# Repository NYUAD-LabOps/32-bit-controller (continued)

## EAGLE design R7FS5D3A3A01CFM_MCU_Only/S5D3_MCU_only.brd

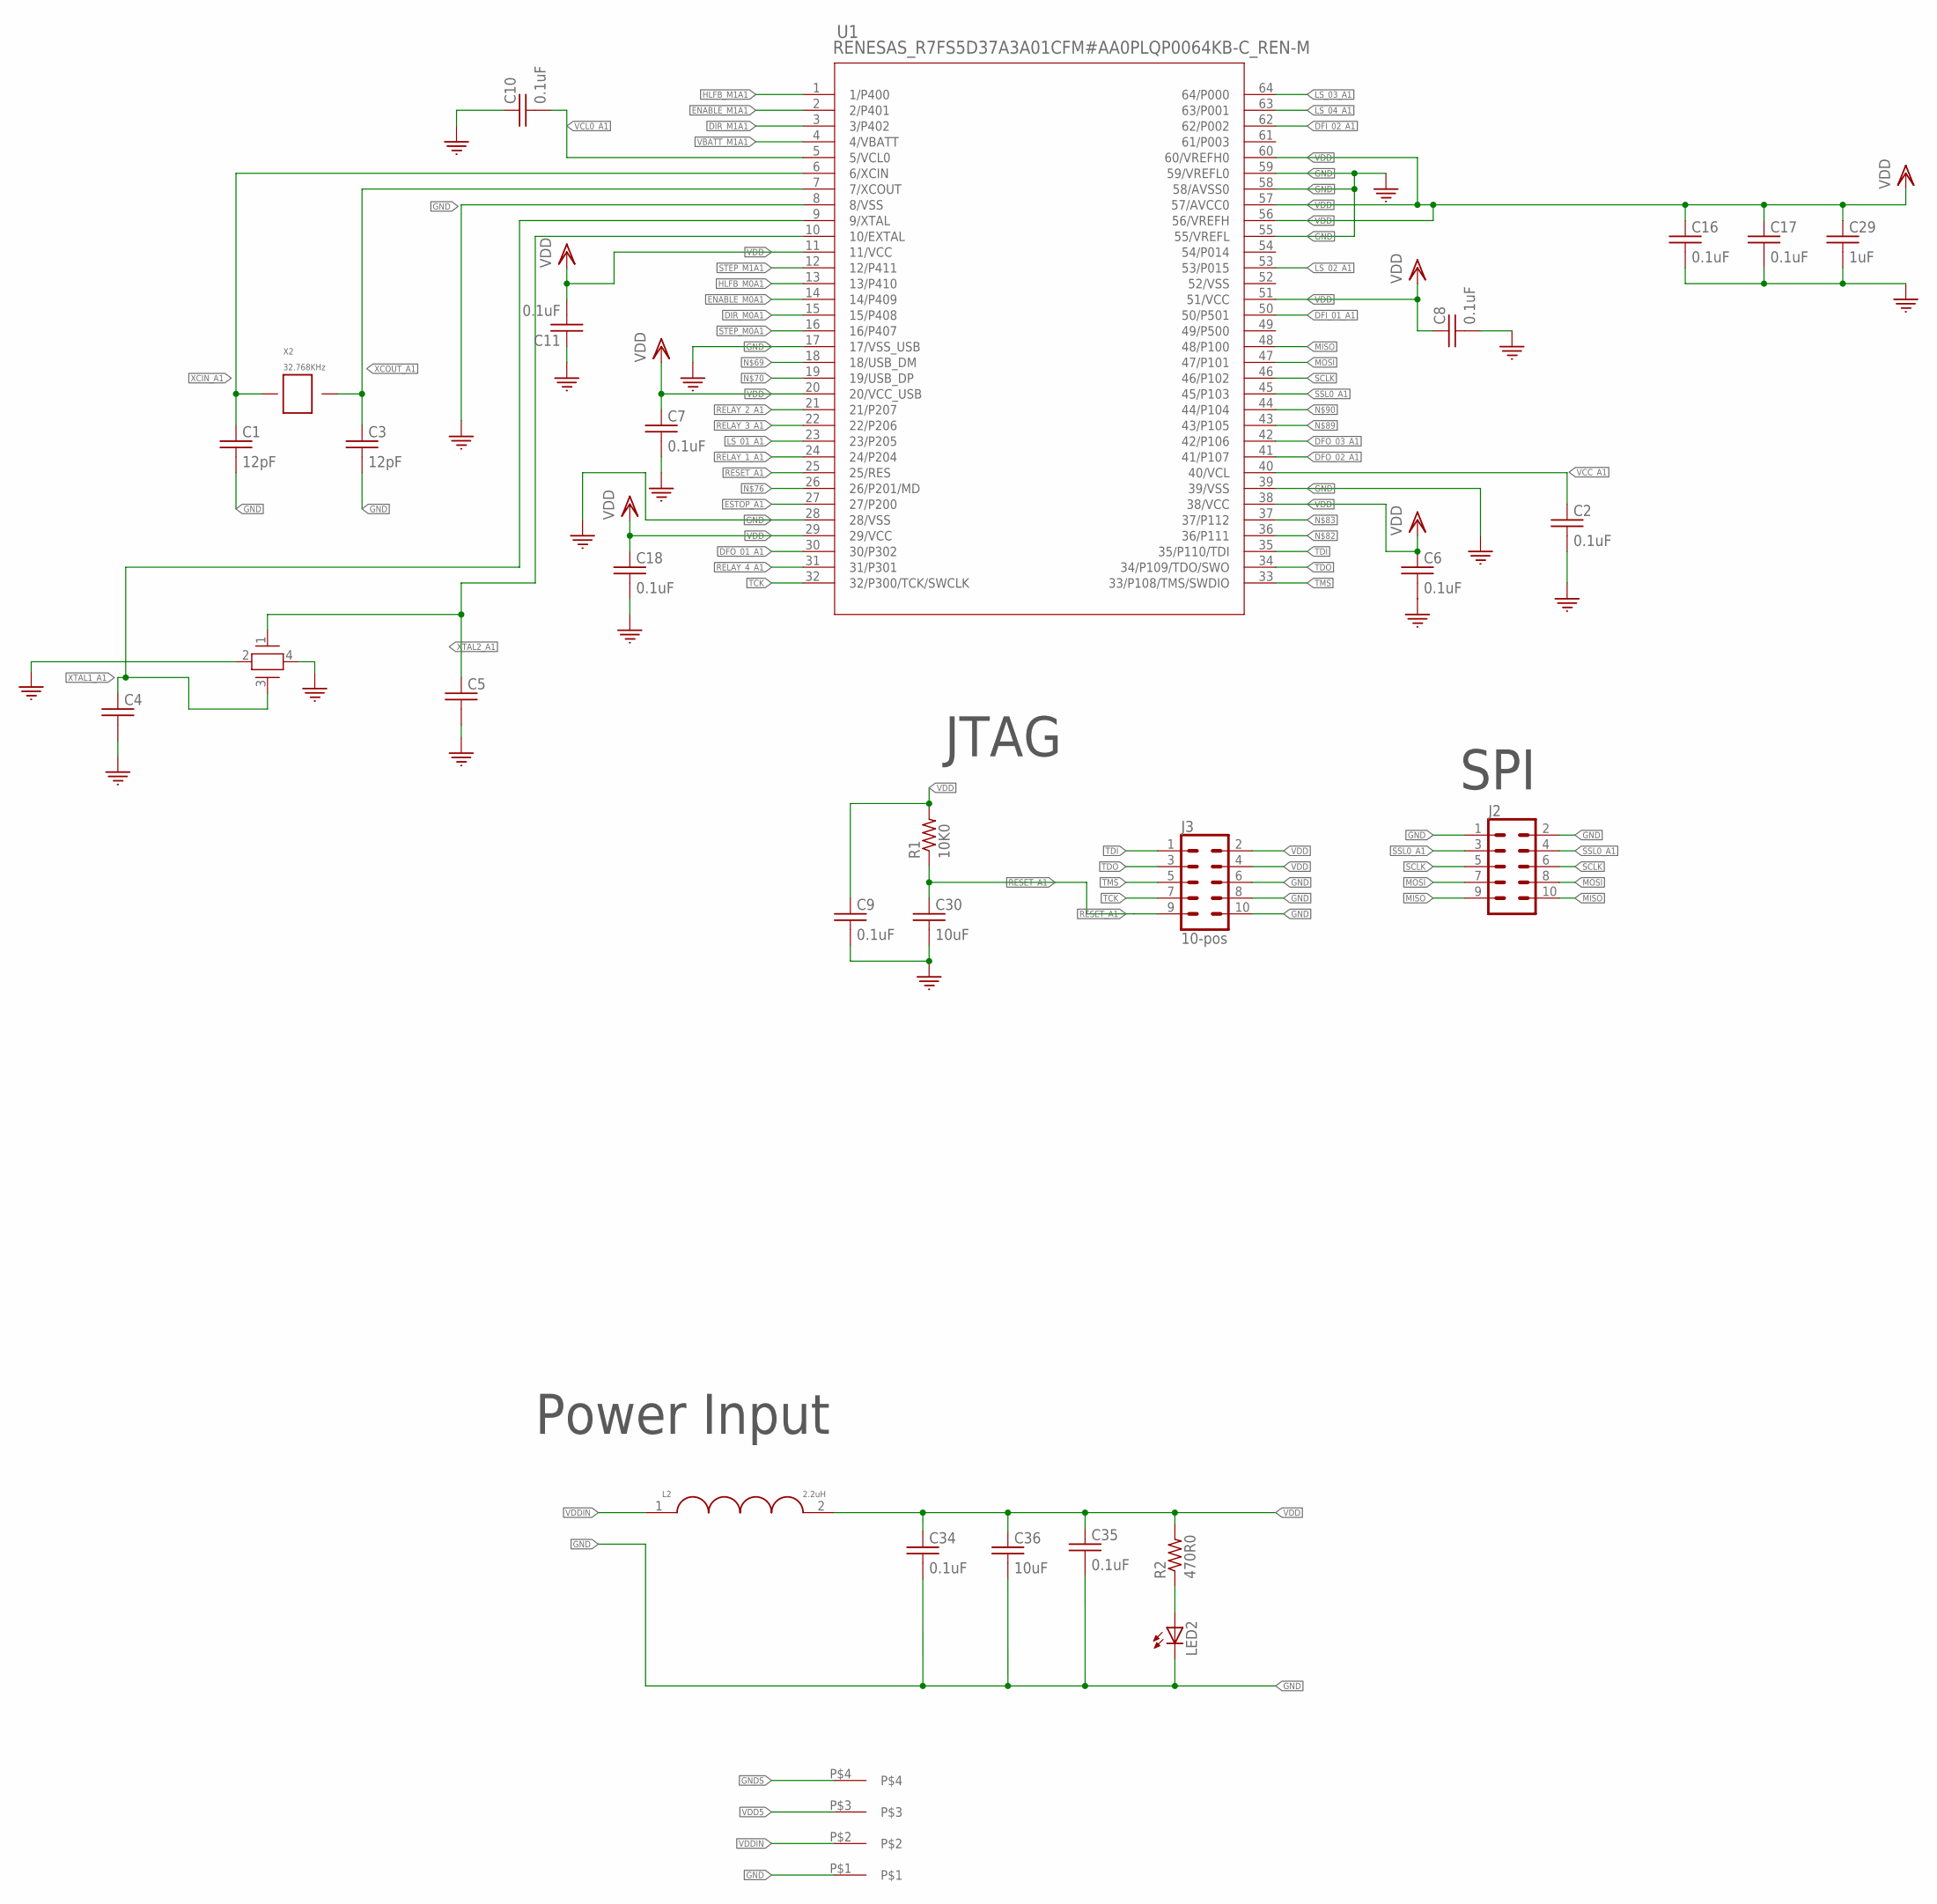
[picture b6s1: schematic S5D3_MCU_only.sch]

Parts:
C1, C3: 12pF; 0402
C2, C6, C7, C8, C9, C10, C11, C16, C17, C18, C34, C35: 0.1uF; 0402
C4, C5: 10pF; 0402
C29: 1uF; 0402
C30, C36: 10uF; 0402
J2: CONN_05X2PTH; 2X5
J3: 10-pos; 2X5
J5: 4-pos; 1X4_3.81MM_PITCH
L2: 2.2uH; 1008
LED2: Green; 0805
R1: 10K0; 0402
R2: 470R0; 0402
U1: RENESAS_R7FS5D37A3A01CFM#AA0PLQP0064KB-C_REN-M; PLQP0064KB-C_REN-M
X2: 32.768KHz; SMD_X_2_PADS
Y1: XTAL_12MHZ_ABM8G-12.000MHZ-B4Y-T; CRYSTAL_ABM8G_ABR

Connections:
DFI_01_A1: U1.50 (50/P501)
DFI_02_A1: U1.62 (62/P002)
DFO_01_A1: U1.30 (30/P302)
DFO_02_A1: U1.41 (41/P107)
DFO_03_A1: U1.42 (42/P106)
DIR_M0A1: U1.15 (15/P408)
DIR_M1A1: U1.3 (3/P402)
ENABLE_M0A1: U1.14 (14/P409)
ENABLE_M1A1: U1.2 (2/P401)
ESTOP_A1: U1.27 (27/P200)
GND: C1.P$2 (2), C2.P$2 (2), C3.P$2 (2), C4.P$2 (2), C5.P$2 (2), C6.P$2 (2), C7.P$2 (2), C8.P$2 (2), C9.P$2 (2), C10.P$1 (1), C11.P$1 (1), C16.P$2 (2), C17.P$2 (2), C18.P$2 (2), C29.P$2 (2), C30.P$2 (2), C34.P$2 (2), C35.P$2 (2), C36.P$2 (2), J2.1, J2.2, J3.6, J3.8, J3.10, J5.P$1, LED2.2 (C), U1.8 (8/VSS), U1.17 (17/VSS_USB), U1.28 (28/VSS), U1.39 (39/VSS), U1.55 (55/VREFL), U1.58 (58/AVSS0), U1.59 (59/VREFL0), Y1.2, Y1.4
GNDS: J5.P$4
HLFB_M0A1: U1.13 (13/P410)
HLFB_M1A1: U1.1 (1/P400)
LS_01_A1: U1.23 (23/P205)
LS_02_A1: U1.53 (53/P015)
LS_03_A1: U1.64 (64/P000)
LS_04_A1: U1.63 (63/P001)
MISO: J2.9, J2.10, U1.48 (48/P100)
MOSI: J2.7, J2.8, U1.47 (47/P101)
unnamed: LED2.1 (A), R2.P$1 (1)
RELAY_1_A1: U1.24 (24/P204)
RELAY_2_A1: U1.21 (21/P207)
RELAY_3_A1: U1.22 (22/P206)
RELAY_4_A1: U1.31 (31/P301)
RESET_A1: C30.P$1 (1), J3.9, R1.P$1 (1), U1.25 (25/RES)
SCLK: J2.5, J2.6, U1.46 (46/P102)
SSL0_A1: J2.3, J2.4, U1.45 (45/P103)
STEP_M0A1: U1.16 (16/P407)
STEP_M1A1: U1.12 (12/P411)
TCK: J3.7, U1.32 (32/P300/TCK/SWCLK)
TDI: J3.1, U1.35 (35/P110/TDI)
TDO: J3.3, U1.34 (34/P109/TDO/SWO)
TMS: J3.5, U1.33 (33/P108/TMS/SWDIO)
VBATT_M1A1: U1.4 (4/VBATT)
VCC_A1: C2.P$1 (1), U1.40 (40/VCL)
VCL0_A1: C10.P$2 (2), U1.5 (5/VCL0)
VDD: C6.P$1 (1), C7.P$1 (1), C8.P$1 (1), C9.P$1 (1), C11.P$2 (2), C16.P$1 (1), C17.P$1 (1), C18.P$1 (1), C29.P$1 (1), C34.P$1 (1), C35.P$1 (1), C36.P$1 (1), J3.2, J3.4, L2.2, R1.P$2 (2), R2.P$2 (2), U1.11 (11/VCC), U1.20 (20/VCC_USB), U1.29 (29/VCC), U1.38 (38/VCC), U1.51 (51/VCC), U1.56 (56/VREFH), U1.57 (57/AVCC0), U1.60 (60/VREFH0)
VDD5: J5.P$3
VDDIN: J5.P$2, L2.1
XCIN_A1: C1.P$1 (1), U1.6 (6/XCIN), X2.P$1
XCOUT_A1: C3.P$1 (1), U1.7 (7/XCOUT), X2.P$2
XTAL1_A1: C4.P$1 (1), U1.9 (9/XTAL), Y1.3
XTAL2_A1: C5.P$1 (1), U1.10 (10/EXTAL), Y1.1

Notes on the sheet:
JTAG
SPI
Power Input

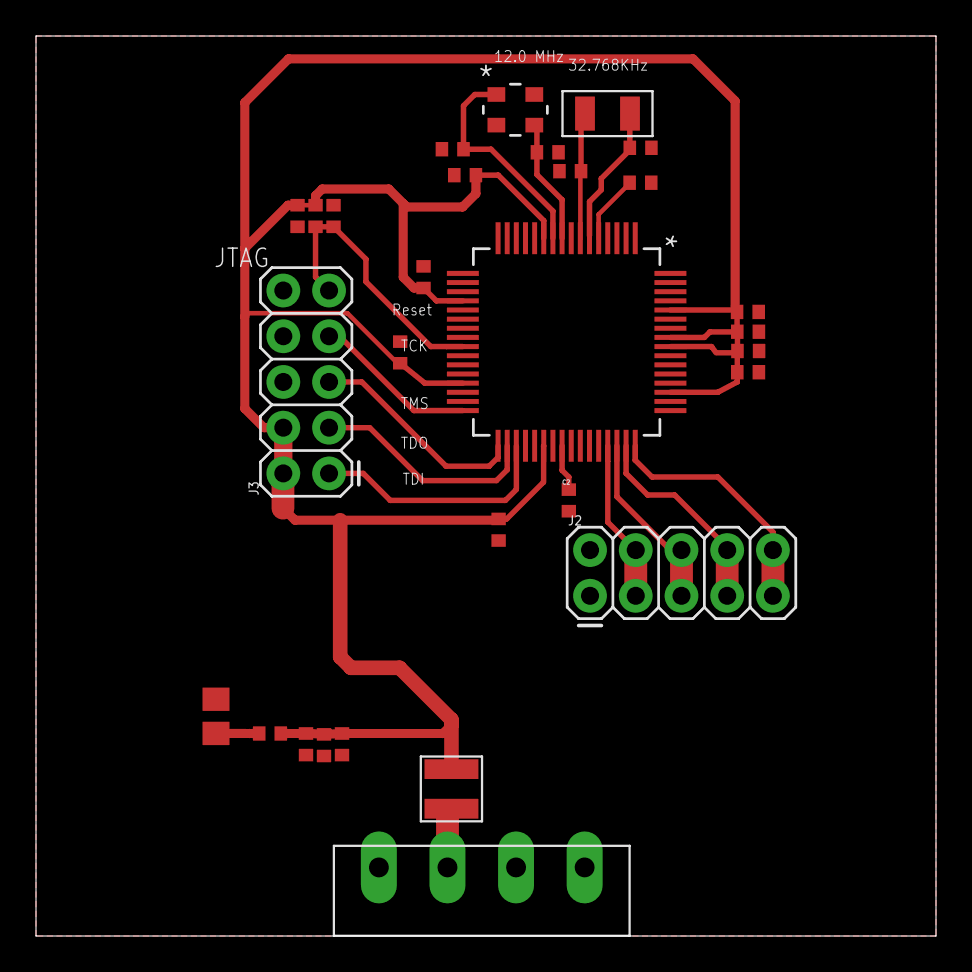
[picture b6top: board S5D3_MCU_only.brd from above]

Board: 2 copper layers, 50.0 x 50.0 mm, 29 parts (0 on the bottom side), 19 nets.
